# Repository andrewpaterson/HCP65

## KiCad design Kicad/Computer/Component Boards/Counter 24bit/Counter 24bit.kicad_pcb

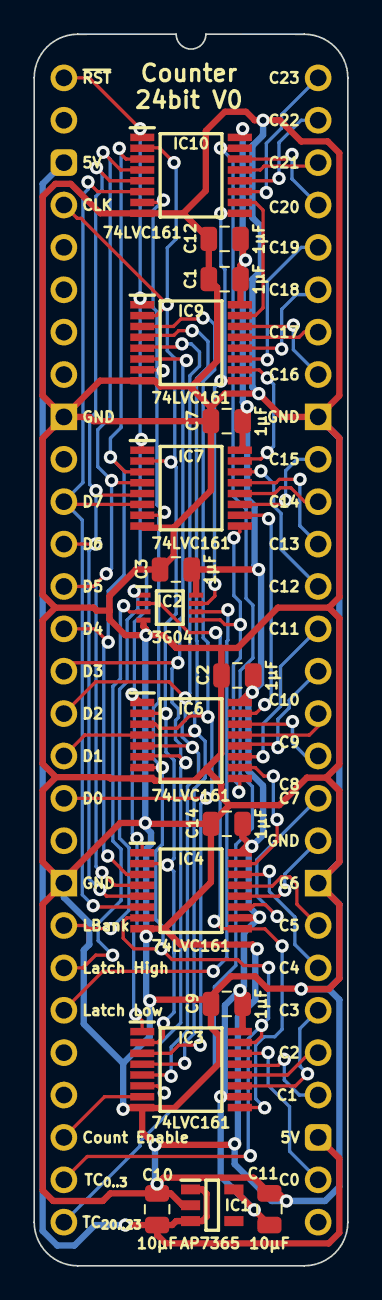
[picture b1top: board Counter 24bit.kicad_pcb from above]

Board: 2 copper layers, 18.8 x 73.8 mm, 18 parts (0 on the bottom side), 50 nets.

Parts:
C1, C2, C3, C7, C9, C12, C14: 1μF; C_0805
C10, C11: 10µF; C_0805
IC1: AP7365-33WG-7; SOT95P285X130-5N
IC2: SN74LVC3G04DCUR; SOP50P310X90-8N
IC3, IC4, IC6, IC7, IC9, IC10: 74LVC161PW,112; SOP65P640X110-16N
J1: Board 2x28 W15.24mm; DIP-56_Board_W15.24mm

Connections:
5V: C10.1, IC1.1 (6VIn), IC1.3 (EN), J1.3, J1.31
/3.3V: C1.1, C2.1, C3.1, C7.1, C9.1, C11.1, C12.1, C14.1, IC1.5 (3.3VOut), IC2.8 (3V), IC3.10 (CET), IC3.16 (3V), IC4.10 (CET), IC4.16 (3V), IC6.16 (3V), IC7.16 (3V), IC9.16 (3V), IC10.16 (3V)
/TC_{4..7}: IC4.15 (TC), IC6.10 (CET)
/TC_{8..11}: IC6.15 (TC), IC7.10 (CET)
/TC_{12..15}: IC7.15 (TC), IC9.10 (CET)
/TC_{16..19}: IC9.15 (TC), IC10.10 (CET)
/~Latch Bank: IC2.7 (1Y), IC9.9 (~PE), IC10.9 (~PE)
/~Latch High: IC2.5 (2Y), IC6.9 (~PE), IC7.9 (~PE)
/~Latch Low: IC2.2 (3Y), IC3.9 (~PE), IC4.9 (~PE)
C0: IC3.14 (Q0), J1.30
C1: IC3.13 (Q1), J1.32
C2: IC3.12 (Q2), J1.33
C3: IC3.11 (Q3), J1.34
C4: IC4.14 (Q0), J1.35
C5: IC4.13 (Q1), J1.36
C6: IC4.12 (Q2), J1.38
C7: IC4.11 (Q3), J1.39
C8: IC6.14 (Q0), J1.40
C9: IC6.13 (Q1), J1.41
C10: IC6.12 (Q2), J1.42
C11: IC6.11 (Q3), J1.43
C12: IC7.14 (Q0), J1.44
C13: IC7.13 (Q1), J1.45
C14: IC7.12 (Q2), J1.46
C15: IC7.11 (Q3), J1.47
C16: IC9.14 (Q0), J1.49
C17: IC9.13 (Q1), J1.50
C18: IC9.12 (Q2), J1.51
C19: IC9.11 (Q3), J1.52
C20: IC10.14 (Q0), J1.53
C21: IC10.13 (Q1), J1.54
C22: IC10.12 (Q2), J1.55
C23: IC10.11 (Q3), J1.56
CLK: IC3.2 (CP), IC4.2 (CP), IC6.2 (CP), IC7.2 (CP), IC9.2 (CP), IC10.2 (CP), J1.4
Count Enable: IC3.7 (CEP), J1.26
D0: IC3.3 (D0), IC6.3 (D0), IC9.3 (D0), J1.18
D1: IC3.4 (D1), IC6.4 (D1), IC9.4 (D1), J1.17
D2: IC3.5 (D2), IC6.5 (D2), IC9.5 (D2), J1.16
D3: IC3.6 (D3), IC6.6 (D3), IC9.6 (D3), J1.15
D4: IC4.3 (D0), IC7.3 (D0), IC10.3 (D0), J1.14
D5: IC4.4 (D1), IC7.4 (D1), IC10.4 (D1), J1.13
D6: IC4.5 (D2), IC7.5 (D2), IC10.5 (D2), J1.12
D7: IC4.6 (D3), IC7.6 (D3), IC10.6 (D3), J1.11
GND: C1.2, C2.2, C3.2, C7.2, C9.2, C10.2, C11.2, C12.2, C14.2, IC1.2 (GND), IC2.4 (GND), IC3.8 (GND), IC4.8 (GND), IC6.8 (GND), IC7.8 (GND), IC9.8 (GND), IC10.8 (GND), J1.9, J1.20, J1.37, J1.48
Latch Bank: IC2.1 (1A), J1.21
Latch High: IC2.3 (2A), J1.22
Latch Low: IC2.6 (3A), J1.23
TC_{0..3}: IC3.15 (TC), IC4.7 (CEP), IC6.7 (CEP), IC7.7 (CEP), IC9.7 (CEP), IC10.7 (CEP), J1.27
TC_{20..23}: IC10.15 (TC), J1.28
~Reset: IC3.1 (~MR), IC4.1 (~MR), IC6.1 (~MR), IC7.1 (~MR), IC9.1 (~MR), IC10.1 (~MR), J1.1

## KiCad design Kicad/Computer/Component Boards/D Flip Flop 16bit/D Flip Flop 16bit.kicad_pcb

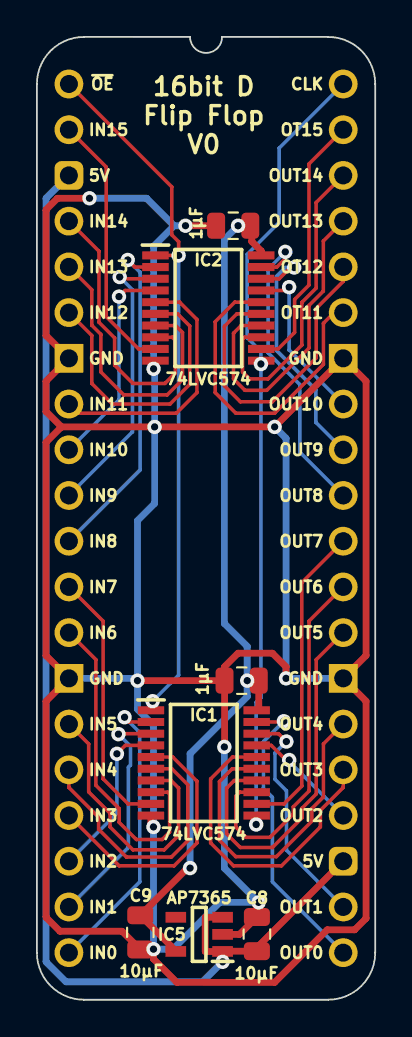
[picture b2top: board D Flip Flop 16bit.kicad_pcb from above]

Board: 2 copper layers, 18.8 x 53.5 mm, 8 parts (0 on the bottom side), 37 nets.

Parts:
C1, C2: 1μF; C_0805
C8, C9: 10µF; C_0805
IC1, IC2: 74LVC574APW,118; SOP65P640X110-20N
IC5: AP7365-33WG-7; SOT95P285X130-5N
J2: Board 2x20 W15.24mm; DIP-40_Board_W15.24mm

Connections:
5V: C8.1, IC5.1 (6VIn), IC5.3 (EN), J2.3, J2.23
/3.3V: C1.1, C2.1, C9.1, IC1.20 (3V), IC2.20 (3V), IC5.5 (3.3VOut)
C0: IC1.2 (D0), J2.20
C1: IC1.3 (D1), J2.19
C2: IC1.4 (D2), J2.18
C3: IC1.5 (D3), J2.17
C4: IC1.6 (D4), J2.16
C5: IC1.7 (D5), J2.15
C6: IC1.8 (D6), J2.13
C7: IC1.9 (D7), J2.12
C8: IC2.2 (D0), J2.11
C9: IC2.3 (D1), J2.10
C10: IC2.4 (D2), J2.9
C11: IC2.5 (D3), J2.8
C12: IC2.6 (D4), J2.6
C13: IC2.7 (D5), J2.5
C14: IC2.8 (D6), J2.4
C15: IC2.9 (D7), J2.2
CLK: IC1.11 (CP), IC2.11 (CP), J2.40
GND: C1.2, C2.2, C8.2, C9.2, IC1.10 (GND), IC2.10 (GND), IC5.2 (GND), J2.7, J2.14, J2.27, J2.34
VA0: IC1.19 (Q0), J2.21
VA1: IC1.18 (Q1), J2.22
VA2: IC1.17 (Q2), J2.24
VA3: IC1.16 (Q3), J2.25
VA4: IC1.15 (Q4), J2.26
VA5: IC1.14 (Q5), J2.28
VA6: IC1.13 (Q6), J2.29
VA7: IC1.12 (Q7), J2.30
VA8: IC2.19 (Q0), J2.31
VA9: IC2.18 (Q1), J2.32
VA10: IC2.17 (Q2), J2.33
VA11: IC2.16 (Q3), J2.35
VA12: IC2.15 (Q4), J2.36
VA13: IC2.14 (Q5), J2.37
VA14: IC2.13 (Q6), J2.38
VA15: IC2.12 (Q7), J2.39
~OE: IC1.1 (~OE), IC2.1 (~OE), J2.1

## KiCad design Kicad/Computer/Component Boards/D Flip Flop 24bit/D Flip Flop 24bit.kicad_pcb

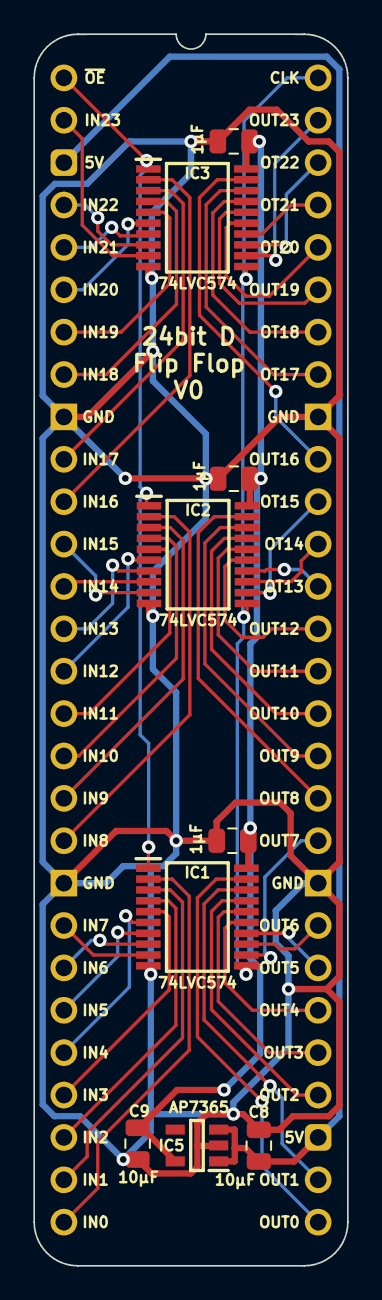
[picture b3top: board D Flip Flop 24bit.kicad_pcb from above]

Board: 2 copper layers, 18.8 x 73.8 mm, 10 parts (0 on the bottom side), 53 nets.

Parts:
C1, C2, C3: 1μF; C_0805
C8, C9: 10µF; C_0805
IC1, IC2, IC3: 74LVC574APW,118; SOP65P640X110-20N
IC5: AP7365-33WG-7; SOT95P285X130-5N
J2: Board 2x28 W15.24mm; DIP-56_Board_W15.24mm

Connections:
5V: C8.1, IC5.1 (6VIn), IC5.3 (EN), J2.3, J2.31
/3.3V: C1.1, C2.1, C3.1, C9.1, IC1.20 (3V), IC2.20 (3V), IC3.20 (3V), IC5.5 (3.3VOut)
C0: IC1.2 (D0), J2.28
C1: IC1.3 (D1), J2.27
C2: IC1.4 (D2), J2.26
C3: IC1.5 (D3), J2.25
C4: IC1.6 (D4), J2.24
C5: IC1.7 (D5), J2.23
C6: IC1.8 (D6), J2.22
C7: IC1.9 (D7), J2.21
C8: IC2.2 (D0), J2.19
C9: IC2.3 (D1), J2.18
C10: IC2.4 (D2), J2.17
C11: IC2.5 (D3), J2.16
C12: IC2.6 (D4), J2.15
C13: IC2.7 (D5), J2.14
C14: IC2.8 (D6), J2.13
C15: IC2.9 (D7), J2.12
C16: IC3.2 (D0), J2.11
C17: IC3.3 (D1), J2.10
C18: IC3.4 (D2), J2.8
C19: IC3.5 (D3), J2.7
C20: IC3.6 (D4), J2.6
C21: IC3.7 (D5), J2.5
C22: IC3.8 (D6), J2.4
C23: IC3.9 (D7), J2.2
CLK: IC1.11 (CP), IC2.11 (CP), IC3.11 (CP), J2.56
GND: C1.2, C2.2, C3.2, C8.2, C9.2, IC1.10 (GND), IC2.10 (GND), IC3.10 (GND), IC5.2 (GND), J2.9, J2.20, J2.37, J2.48
VA0: IC1.19 (Q0), J2.29
VA1: IC1.18 (Q1), J2.30
VA2: IC1.17 (Q2), J2.32
VA3: IC1.16 (Q3), J2.33
VA4: IC1.15 (Q4), J2.34
VA5: IC1.14 (Q5), J2.35
VA6: IC1.13 (Q6), J2.36
VA7: IC1.12 (Q7), J2.38
VA8: IC2.19 (Q0), J2.39
VA9: IC2.18 (Q1), J2.40
VA10: IC2.17 (Q2), J2.41
VA11: IC2.16 (Q3), J2.42
VA12: IC2.15 (Q4), J2.43
VA13: IC2.14 (Q5), J2.44
VA14: IC2.13 (Q6), J2.45
VA15: IC2.12 (Q7), J2.46
VA16: IC3.19 (Q0), J2.47
VA17: IC3.18 (Q1), J2.49
VA18: IC3.17 (Q2), J2.50
VA19: IC3.16 (Q3), J2.51
VA20: IC3.15 (Q4), J2.52
VA21: IC3.14 (Q5), J2.53
VA22: IC3.13 (Q6), J2.54
VA23: IC3.12 (Q7), J2.55
~OE: IC1.1 (~OE), IC2.1 (~OE), IC3.1 (~OE), J2.1

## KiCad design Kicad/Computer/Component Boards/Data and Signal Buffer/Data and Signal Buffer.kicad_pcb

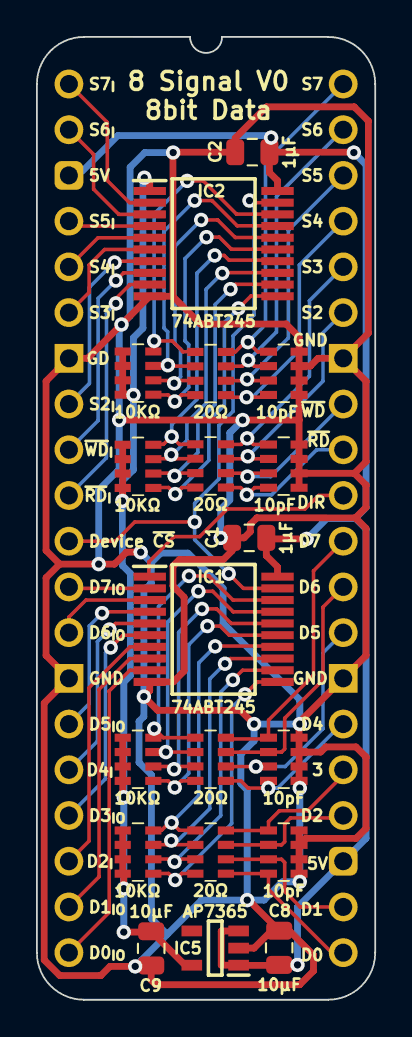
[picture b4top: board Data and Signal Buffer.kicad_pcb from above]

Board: 2 copper layers, 18.8 x 53.5 mm, 20 parts (0 on the bottom side), 53 nets.

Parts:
C1, C2: 1μF; C_0805
C8, C9: 10µF; C_0805
CN1, CN2, CN3, CN4: CA0612KRX7R9BB100
IC1, IC2: SN74ABT245BDBR; SOP65P780X200-20N
IC5: AP7365-33WG-7; SOT95P285X130-5N
J2: Board 2x20 W15.24mm; DIP-40_Board_W15.24mm
RN1, RN2, RN3, RN4: CAY16-103J4LF; CAY16-J4
RN5, RN6, RN7, RN8: CAY16-200J4LF; CAY16-F4

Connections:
5V: C1.1, C2.1, C8.1, IC1.20 (5V), IC2.20 (5V), IC5.1 (6VIn), IC5.3 (EN), J2.3, J2.23
/3.3V: C9.1, IC2.1 (DIR), IC5.5 (3.3VOut), RN1.5 (R4), RN1.6 (R3), RN1.7 (R2), RN1.8 (R1), RN2.5 (R4), RN2.6 (R3), RN2.7 (R2), RN2.8 (R1), RN3.5 (R4), RN3.6 (R3), RN3.7 (R2), RN3.8 (R1), RN4.5 (R4), RN4.6 (R3), RN4.7 (R2), RN4.8 (R1)
/D0: IC1.11 (B7), RN2.1 (R1), RN6.8 (R1)
/D1: IC1.12 (B6), RN2.2 (R2), RN6.7 (R2)
/D2: IC1.13 (B5), RN2.3 (R3), RN6.6 (R3)
/D3: IC1.14 (B4), RN2.4 (R4), RN6.5 (R4)
/D4: IC1.15 (B3), RN1.1 (R1), RN5.8 (R1)
/D5: IC1.16 (B2), RN1.2 (R2), RN5.7 (R2)
/D6: IC1.17 (B1), RN1.3 (R3), RN5.6 (R3)
/D7: IC1.18 (B0), RN1.4 (R4), RN5.5 (R4)
/S2: IC2.13 (B5), RN4.3 (R3), RN7.6 (R3)
/S3: IC2.14 (B4), RN4.4 (R4), RN7.5 (R4)
/S4: IC2.15 (B3), RN3.1 (R1), RN8.8 (R1)
/S5: IC2.16 (B2), RN3.2 (R2), RN8.7 (R2)
/S6: IC2.17 (B1), RN3.3 (R3), RN8.6 (R3)
/S7: IC2.18 (B0), RN3.4 (R4), RN8.5 (R4)
/~RD: IC2.11 (B7), RN4.1 (R1), RN7.8 (R1)
/~WD: IC2.12 (B6), RN4.2 (R2), RN7.7 (R2)
D0_{IN/OUT}: IC1.9 (A7), J2.20
D0_{s}: CN2.4, J2.21, RN6.1 (R1)
D1_{IN/OUT}: IC1.8 (A6), J2.19
D1_{s}: CN2.3, J2.22, RN6.2 (R2)
D2_{IN/OUT}: IC1.7 (A5), J2.18
D2_{s}: CN2.2, J2.24, RN6.3 (R3)
D3_{IN/OUT}: IC1.6 (A4), J2.17
D3_{s}: CN2.1, J2.25, RN6.4 (R4)
D4_{IN/OUT}: IC1.5 (A3), J2.16
D4_{s}: CN1.4, J2.26, RN5.1 (R1)
D5_{IN/OUT}: IC1.4 (A2), J2.15
D5_{s}: CN1.3, J2.28, RN5.2 (R2)
D6_{IN/OUT}: IC1.3 (A1), J2.13
D6_{s}: CN1.2, J2.29, RN5.3 (R3)
D7_{IN/OUT}: IC1.2 (A0), J2.12
D7_{s}: CN1.1, J2.30, RN5.4 (R4)
DIR: IC1.1 (DIR), J2.31
Device ~CS: IC1.19 (~OE), IC2.19 (~OE), J2.11
GND: C1.2, C2.2, C8.2, C9.2, CN1.5, CN1.6, CN1.7, CN1.8, CN2.5, CN2.6, CN2.7, CN2.8, CN3.5, CN3.6, CN3.7, CN3.8, CN4.5, CN4.6, CN4.7, CN4.8, IC1.10 (GND), IC2.10 (GND), IC5.2 (GND), J2.7, J2.14, J2.27, J2.34
S2_{IN}: IC2.7 (A5), J2.8
S2_{s}: CN3.2, J2.35, RN7.3 (R3)
S3_{IN}: IC2.6 (A4), J2.6
S3_{s}: CN3.1, J2.36, RN7.4 (R4)
S4_{IN}: IC2.5 (A3), J2.5
S4_{s}: CN4.4, J2.37, RN8.1 (R1)
S5_{IN}: IC2.4 (A2), J2.4
S5_{s}: CN4.3, J2.38, RN8.2 (R2)
S6_{IN}: IC2.3 (A1), J2.2
S6_{s}: CN4.2, J2.39, RN8.3 (R3)
S7_{IN}: IC2.2 (A0), J2.1
S7_{s}: CN4.1, J2.40, RN8.4 (R4)
~RD_{IN}: IC2.9 (A7), J2.10
~RD_{s}: CN3.4, J2.32, RN7.1 (R1)
~WD_{IN}: IC2.8 (A6), J2.9
~WD_{s}: CN3.3, J2.33, RN7.2 (R2)

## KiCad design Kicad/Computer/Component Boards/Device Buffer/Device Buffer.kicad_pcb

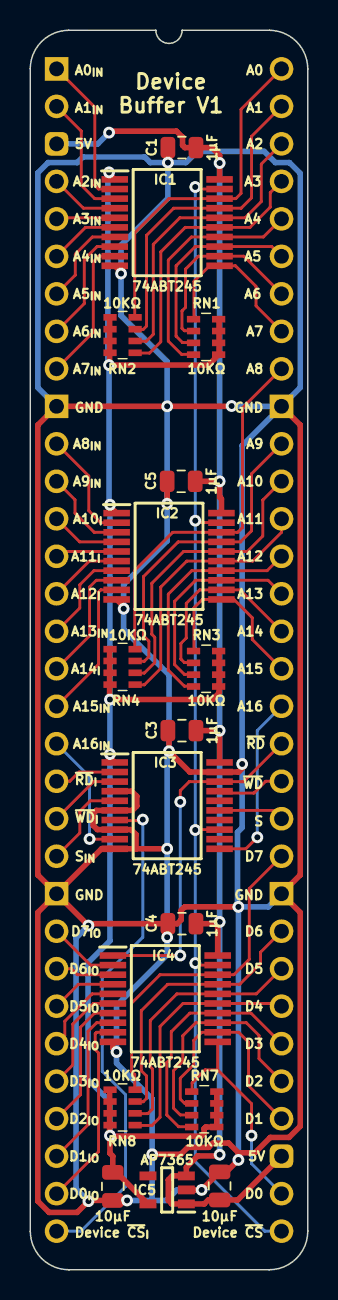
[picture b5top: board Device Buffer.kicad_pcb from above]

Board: 2 copper layers, 18.8 x 84.0 mm, 18 parts (0 on the bottom side), 61 nets.

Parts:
C1, C3, C4, C5: 1μF; C_0805
C8, C9: 10µF; C_0805
IC1, IC2, IC3, IC4: SN74ABT245BDBR; SOP65P780X200-20N
IC5: AP7365-33WG-7; SOT95P285X130-5N
J2: Board 2x32 W15.24mm; DIP-64_Board_W15.24mm
RN1, RN2, RN3, RN4, RN7, RN8: CAY16-103J4LF; CAY16-J4

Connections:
5V: C1.1, C3.1, C4.1, C5.1, C8.1, IC1.20 (5V), IC2.20 (5V), IC3.20 (5V), IC4.20 (5V), IC5.1 (6VIn), IC5.3 (EN), J2.3, J2.35
/3.3V: C9.1, IC1.1 (DIR), IC2.1 (DIR), IC3.1 (DIR), IC5.5 (3.3VOut), RN1.5 (R4), RN1.6 (R3), RN1.7 (R2), RN1.8 (R1), RN2.5 (R4), RN2.6 (R3), RN2.7 (R2), RN2.8 (R1), RN3.5 (R4), RN3.6 (R3), RN3.7 (R2), RN3.8 (R1), RN4.5 (R4), RN4.6 (R3), RN4.7 (R2), RN4.8 (R1), RN7.5 (R4), RN7.6 (R3), RN7.7 (R2), RN7.8 (R1), RN8.5 (R4), RN8.6 (R3), RN8.7 (R2), RN8.8 (R1)
A0: IC1.18 (B0), J2.64, RN2.4 (R4)
A0_{IN}: IC1.2 (A0), J2.1
A1: IC1.17 (B1), J2.63, RN2.3 (R3)
A1_{IN}: IC1.3 (A1), J2.2
A2: IC1.16 (B2), J2.62, RN2.2 (R2)
A2_{IN}: IC1.4 (A2), J2.4
A3: IC1.15 (B3), J2.61, RN2.1 (R1)
A3_{IN}: IC1.5 (A3), J2.5
A4: IC1.14 (B4), J2.60, RN1.4 (R4)
A4_{IN}: IC1.6 (A4), J2.6
A5: IC1.13 (B5), J2.59, RN1.3 (R3)
A5_{IN}: IC1.7 (A5), J2.7
A6: IC1.12 (B6), J2.58, RN1.2 (R2)
A6_{IN}: IC1.8 (A6), J2.8
A7: IC1.11 (B7), J2.57, RN1.1 (R1)
A7_{IN}: IC1.9 (A7), J2.9
A8: IC2.18 (B0), J2.56, RN4.4 (R4)
A8_{IN}: IC2.2 (A0), J2.11
A9: IC2.17 (B1), J2.54, RN4.3 (R3)
A9_{IN}: IC2.3 (A1), J2.12
A10: IC2.16 (B2), J2.53, RN4.2 (R2)
A10_{IN}: IC2.4 (A2), J2.13
A11: IC2.15 (B3), J2.52, RN4.1 (R1)
A11_{IN}: IC2.5 (A3), J2.14
A12: IC2.14 (B4), J2.51, RN3.4 (R4)
A12_{IN}: IC2.6 (A4), J2.15
A13: IC2.13 (B5), J2.50, RN3.3 (R3)
A13_{IN}: IC2.7 (A5), J2.16
A14: IC2.12 (B6), J2.49, RN3.2 (R2)
A14_{IN}: IC2.8 (A6), J2.17
A15: IC2.11 (B7), J2.48, RN3.1 (R1)
A15_{IN}: IC2.9 (A7), J2.18
A16: IC3.11 (B7), J2.47
A16_{IN}: IC3.9 (A7), J2.19
D0: IC4.11 (B7), J2.34, RN7.1 (R1)
D0_{IN/OUT}: IC4.9 (A7), J2.31
D1: IC4.12 (B6), J2.36, RN7.2 (R2)
D1_{IN/OUT}: IC4.8 (A6), J2.30
D2: IC4.13 (B5), J2.37, RN7.3 (R3)
D2_{IN/OUT}: IC4.7 (A5), J2.29
D3: IC4.14 (B4), J2.38, RN7.4 (R4)
D3_{IN/OUT}: IC4.6 (A4), J2.28
D4: IC4.15 (B3), J2.39, RN8.1 (R1)
D4_{IN/OUT}: IC4.5 (A3), J2.27
D5: IC4.16 (B2), J2.40, RN8.2 (R2)
D5_{IN/OUT}: IC4.4 (A2), J2.26
D6: IC4.17 (B1), J2.41, RN8.3 (R3)
D6_{IN/OUT}: IC4.3 (A1), J2.25
D7: IC4.18 (B0), J2.43, RN8.4 (R4)
D7_{IN/OUT}: IC4.2 (A0), J2.24
Device ~CS: IC1.19 (~OE), IC2.19 (~OE), IC3.13 (B5), IC4.19 (~OE), J2.33
Device ~CS_{IN}: IC3.7 (A5), J2.32
GND: C1.2, C3.2, C4.2, C5.2, C8.2, C9.2, IC1.10 (GND), IC2.10 (GND), IC3.4 (A2), IC3.6 (A4), IC3.8 (A6), IC3.10 (GND), IC3.19 (~OE), IC4.10 (GND), IC5.2 (GND), J2.10, J2.23, J2.42, J2.55
S: IC3.15 (B3), J2.44
S_{IN}: IC3.5 (A3), J2.22
~RD: IC3.18 (B0), IC4.1 (DIR), J2.46
~RD_{IN}: IC3.2 (A0), J2.20
~WD: IC3.17 (B1), J2.45
~WD_{IN}: IC3.3 (A1), J2.21

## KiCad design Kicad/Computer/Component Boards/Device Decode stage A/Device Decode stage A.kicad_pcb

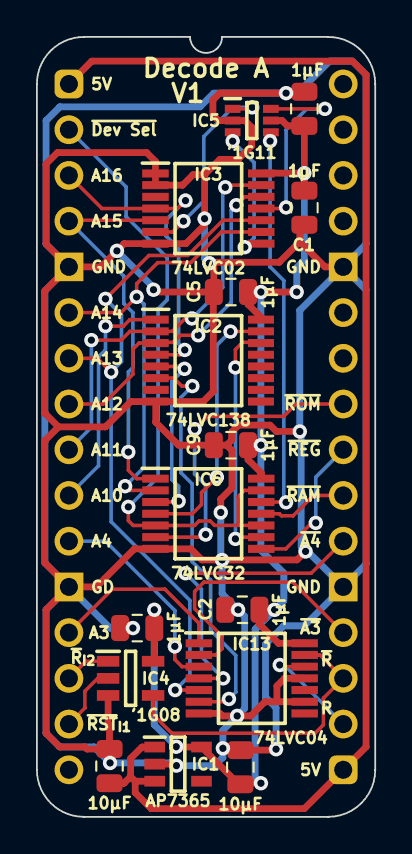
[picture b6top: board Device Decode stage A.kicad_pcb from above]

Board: 2 copper layers, 18.8 x 43.3 mm, 16 parts (0 on the bottom side), 30 nets.

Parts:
C1, C2, C3, C5, C9, C12: 1μF; C_0805
C10, C11: 10µF; C_0805
IC1: AP7365-33WG-7; SOT95P285X130-5N
IC2: 74LVC138APW-Q100J; SOP65P640X110-16N
IC3: 74LVC02APW,118; SOP65P640X110-14N
IC4: 74LVC1G08GV,125; SOT95P275X110-5N
IC5: 74LVC1G11GW-Q100H; SOP65P210X110-6N
IC6: 74LVC32APW,118; SOP65P640X110-14N
IC13: 74LVC04APW,118; SOP65P640X110-14N
J1: Board 2x16 W15.24mm; DIP-32_Board_W15.24mm

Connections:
5V: C10.1, IC1.1 (6VIn), IC1.3 (EN), J1.1, J1.17
/3.3V: C1.1, C2.1, C3.1, C5.1, C9.1, C11.1, C12.1, IC1.5 (3.3VOut), IC2.16 (3V), IC3.14 (3V), IC4.5 (3V), IC5.5 (3V), IC6.14 (3V), IC13.14 (3V)
/A15+A14: IC2.5 (~E2), IC6.3 (1Y)
/~A11+A12: IC3.11 (4Y), IC5.6 (C)
/~A13+A14: IC3.8 (3Y), IC5.3 (B)
/~A13: IC2.6 (E3), IC13.6 (3Y)
/~A16+A15: IC3.6 (2Y), IC5.1 (A)
/~Device RAM_{part}: IC5.4 (Y), IC6.12 (4A)
/~Device ROM_{part}: IC2.15 (~Y0), IC6.4 (2A)
/~Device Registers_{part}: IC2.14 (~Y1), IC6.9 (3A)
A3: IC13.1 (1A), J1.13
A4: IC13.3 (2A), J1.11
A10: IC2.1 (A0), J1.10
A11: IC2.2 (A1), IC3.13 (4B), J1.9
A12: IC2.3 (A2), IC3.12 (4A), J1.8
A13: IC3.10 (3B), IC13.5 (3A), J1.7
A14: IC3.9 (3A), IC6.2 (1B), J1.6
A15: IC3.5 (2B), IC6.1 (1A), J1.4
A16: IC2.4 (~E1), IC3.4 (2A), J1.3
GND: C1.2, C2.2, C3.2, C5.2, C9.2, C10.2, C11.2, C12.2, IC1.2 (GND), IC2.8 (GND), IC3.1 (1A), IC3.2 (1B), IC3.7 (GND), IC4.3 (GND), IC5.2 (GND), IC6.7 (GND), IC13.7 (GND), IC13.9 (4A), IC13.11 (5A), J1.5, J1.12, J1.21, J1.28
Reset: IC13.12 (6Y), J1.18
~A3: IC13.2 (1Y), J1.20
~A4: IC13.4 (2Y), J1.22
~Device RAM: IC6.11 (4Y), J1.23
~Device ROM: IC6.6 (2Y), J1.25
~Device Registers: IC6.8 (3Y), J1.24
~Device Select: IC6.5 (2B), IC6.10 (3B), IC6.13 (4B), J1.2
~Reset: IC4.4 (Y), IC13.13 (6A), J1.19
~Reset_{IN1}: IC4.2 (A), J1.15
~Reset_{IN2}: IC4.1 (B), J1.14

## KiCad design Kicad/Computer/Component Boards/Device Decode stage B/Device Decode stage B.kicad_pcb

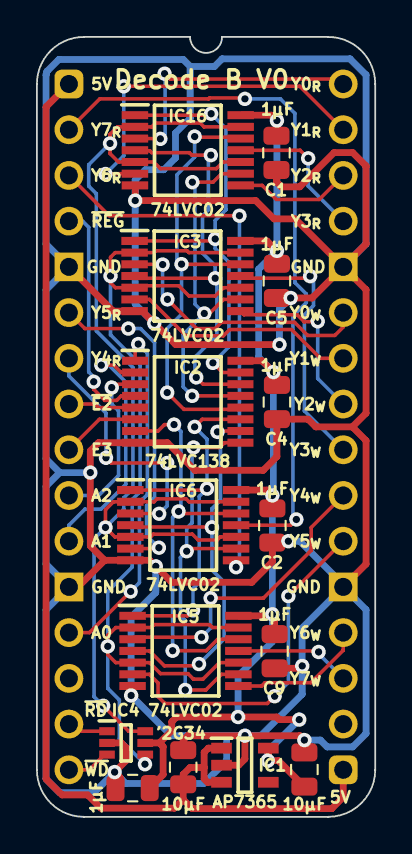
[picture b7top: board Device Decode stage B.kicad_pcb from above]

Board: 2 copper layers, 18.8 x 43.3 mm, 16 parts (0 on the bottom side), 37 nets.

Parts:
C1, C2, C3, C4, C5, C9: 1μF; C_0805
C10, C11: 10µF; C_0805
IC1: AP7365-33WG-7; SOT95P285X130-5N
IC2: 74LVC138APW-Q100J; SOP65P640X110-16N
IC3, IC5, IC6, IC16: 74LVC02APW,118; SOP65P640X110-14N
IC4: 74LVC2G34GW,125; 74LVC2G34GW125
J1: Board 2x16 W15.24mm; DIP-32_Board_W15.24mm

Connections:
5V: C10.1, IC1.1 (6VIn), IC1.3 (EN), J1.1, J1.17
/3.3V: C1.1, C2.1, C3.1, C4.1, C5.1, C9.1, C11.1, IC1.5 (3.3VOut), IC2.16 (3V), IC3.14 (3V), IC4.5 (3V), IC5.14 (3V), IC6.14 (3V), IC16.14 (3V)
/~RD: IC4.6 (1Y), IC6.2 (1B), IC6.5 (2B), IC6.10 (3B), IC6.13 (4B), IC16.2 (1B), IC16.5 (2B), IC16.10 (3B), IC16.13 (4B)
/~WD: IC3.2 (1B), IC3.5 (2B), IC3.10 (3B), IC3.13 (4B), IC4.4 (2Y), IC5.2 (1B), IC5.5 (2B), IC5.10 (3B), IC5.13 (4B)
/~Y0: IC2.15 (~Y0), IC3.1 (1A), IC16.1 (1A)
/~Y1: IC2.14 (~Y1), IC3.4 (2A), IC16.4 (2A)
/~Y2: IC2.13 (~Y2), IC3.9 (3A), IC16.9 (3A)
/~Y3: IC2.12 (~Y3), IC3.12 (4A), IC16.12 (4A)
/~Y4: IC2.11 (~Y4), IC5.1 (1A), IC6.1 (1A)
/~Y5: IC2.10 (~Y5), IC5.4 (2A), IC6.4 (2A)
/~Y6: IC2.9 (~Y6), IC5.9 (3A), IC6.9 (3A)
/~Y7: IC2.7 (~Y7), IC5.12 (4A), IC6.12 (4A)
A0: IC2.1 (A0), J1.13
A1: IC2.2 (A1), J1.11
A2: IC2.3 (A2), J1.10
E3: IC2.6 (E3), J1.9
GND: C1.2, C2.2, C3.2, C4.2, C5.2, C9.2, C10.2, C11.2, IC1.2 (GND), IC2.8 (GND), IC3.7 (GND), IC4.2 (GND), IC5.7 (GND), IC6.7 (GND), IC16.7 (GND), J1.5, J1.12, J1.21, J1.28
Y0+R: IC16.3 (1Y), J1.32
Y0+W: IC3.3 (1Y), J1.27
Y1+R: IC16.6 (2Y), J1.31
Y1+W: IC3.6 (2Y), J1.26
Y2+R: IC16.8 (3Y), J1.30
Y2+W: IC3.8 (3Y), J1.25
Y3+R: IC16.11 (4Y), J1.29
Y3+W: IC3.11 (4Y), J1.24
Y4+R: IC6.3 (1Y), J1.7
Y4+W: IC5.3 (1Y), J1.23
Y5+R: IC6.6 (2Y), J1.6
Y5+W: IC5.6 (2Y), J1.22
Y6+R: IC6.8 (3Y), J1.3
Y6+W: IC5.8 (3Y), J1.20
Y7+R: IC6.11 (4Y), J1.2
Y7+W: IC5.11 (4Y), J1.19
~Device Registers: IC2.4 (~E1), J1.4
~E2: IC2.5 (~E2), J1.8
~RD_{IN}: IC4.1 (1A), J1.15
~WD_{IN}: IC4.3 (2A), J1.16

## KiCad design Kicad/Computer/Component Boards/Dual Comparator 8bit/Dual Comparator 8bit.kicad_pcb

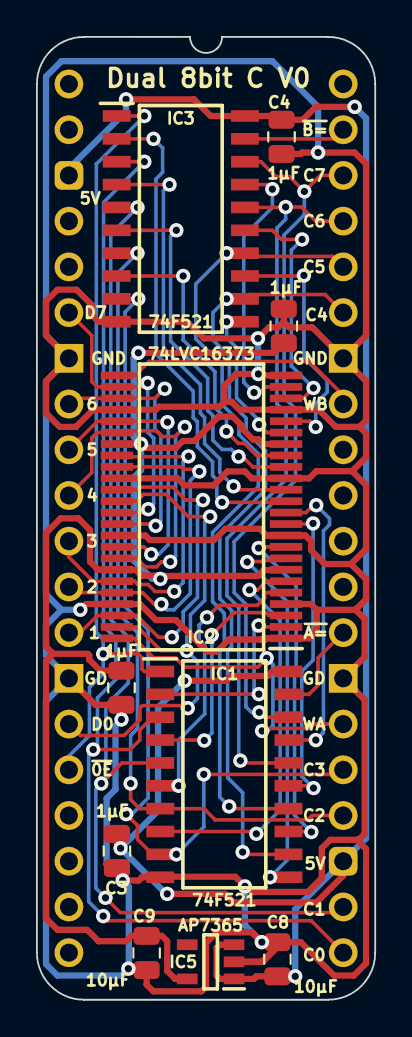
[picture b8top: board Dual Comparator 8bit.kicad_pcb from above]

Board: 2 copper layers, 18.8 x 53.5 mm, 11 parts (0 on the bottom side), 40 nets.

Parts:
C1, C2, C3, C4: 1μF; C_0805
C8, C9: 10µF; C_0805
IC1, IC3: SN74F521NSR; SOIC127P780X200-20N
IC2: 74LVC16373ADL,118; SOP64P1025X280-48N
IC5: AP7365-33WG-7; SOT95P285X130-5N
J2: Board 2x20 W15.24mm; DIP-40_Board_W15.24mm

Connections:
5V: C3.1, C4.1, C8.1, IC1.20 (5V), IC3.20 (5V), IC5.1 (6VIn), IC5.3 (EN), J2.3, J2.23
/3.3V: C1.1, C2.1, C9.1, IC2.7 (3V), IC2.18 (3V), IC2.31 (3V), IC2.42 (3V), IC5.5 (3.3VOut)
/A0: IC1.2 (P0), IC2.2 (1Q0)
/A1: IC1.4 (P1), IC2.3 (1Q1)
/A2: IC1.6 (P2), IC2.5 (1Q2)
/A3: IC1.8 (P3), IC2.6 (1Q3)
/A4: IC1.11 (P4), IC2.8 (1Q4)
/A5: IC1.13 (P5), IC2.9 (1Q5)
/A6: IC1.15 (P6), IC2.11 (1Q6)
/A7: IC1.17 (P7), IC2.12 (1Q7)
/B0: IC2.13 (2Q0), IC3.2 (P0)
/B1: IC2.14 (2Q1), IC3.4 (P1)
/B2: IC2.16 (2Q2), IC3.6 (P2)
/B3: IC2.17 (2Q3), IC3.8 (P3)
/B4: IC2.19 (2Q4), IC3.11 (P4)
/B5: IC2.20 (2Q5), IC3.13 (P5)
/B6: IC2.22 (2Q6), IC3.15 (P6)
/B7: IC2.23 (2Q7), IC3.17 (P7)
C0: IC1.3 (Q0), IC3.3 (Q0), J2.21
C1: IC1.5 (Q1), IC3.5 (Q1), J2.22
C2: IC1.7 (Q2), IC3.7 (Q2), J2.24
C3: IC1.9 (Q3), IC3.9 (Q3), J2.25
C4: IC1.12 (Q4), IC3.12 (Q4), J2.35
C5: IC1.14 (Q5), IC3.14 (Q5), J2.36
C6: IC1.16 (Q6), IC3.16 (Q6), J2.37
C7: IC1.18 (Q7), IC3.18 (Q7), J2.38
D0: IC2.36 (2D0), IC2.47 (1D0), J2.15
D1: IC2.35 (2D1), IC2.46 (1D1), J2.13
D2: IC2.33 (2D2), IC2.44 (1D2), J2.12
D3: IC2.32 (2D3), IC2.43 (1D3), J2.11
D4: IC2.30 (2D4), IC2.41 (1D4), J2.10
D5: IC2.29 (2D5), IC2.40 (1D5), J2.9
D6: IC2.27 (2D6), IC2.38 (1D6), J2.8
D7: IC2.26 (2D7), IC2.37 (1D7), J2.6
GND: C1.2, C2.2, C3.2, C4.2, C8.2, C9.2, IC1.10 (GND), IC2.1 (1~OE), IC2.4 (GND), IC2.10 (GND), IC2.15 (GND), IC2.21 (GND), IC2.24 (2~OE), IC2.28 (GND), IC2.34 (GND), IC2.39 (GND), IC2.45 (GND), IC3.10 (GND), IC5.2 (GND), J2.7, J2.14, J2.27, J2.34
Write A: IC2.48 (1LE), J2.26
Write B: IC2.25 (2LE), J2.33
~A=C: IC1.19 (~P=Q), J2.28
~B=C: IC3.19 (~P=Q), J2.39
~OE: IC1.1 (~OE), IC3.1 (~OE), J2.16
